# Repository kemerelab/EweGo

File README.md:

# EweGo

**Extensible Wearable for Egocentric and Group Observation**

EweGo is an open, animal-borne wearable that records the sensorium of each
animal in a group. It captures synchronized vision, audio, motion and RTK position, so we
can study collective behavior such as flocking, social learning and responses
to stress, with the aim of bringing it into neuroscience experiments. It was
built for sheep and is meant to be adapted to other species.

Each wearable is a Raspberry Pi CM4 on the **eweSAW** carrier board, with two
USB cameras, a u-blox ZED-X20P GNSS receiver, a BNO055 IMU, stereo
microphones and a battery fuel gauge. Every sample gets a precise timestamp.
It mounts on a collar or on a head halter.

| Folder | Contents |
|---|---|
| `Hardware/` | eweSAW carrier, camera hub and EweFeel IMU boards (KiCad), case designs ([details](Hardware/README.md)) |
| `Firmware/` | sensor loggers and test tools |
| `image/` | CI-built, ready-to-flash image ([details](image/README.md)) |

## Flashing a wearable

In Raspberry Pi Imager, open *Options → Content Repository* and enter
`https://github.com/kemerelab/EweGo/releases/latest/download/imager.json`.
Pick the EweGo image, set the hostname, user and Wi-Fi, and flash.

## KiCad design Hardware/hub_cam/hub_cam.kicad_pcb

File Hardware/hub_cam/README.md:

# hub_cam: USB hub carrier for two cameras plus the hub_imu module

**Status:** schematic and PCB layout done, DRC clean (0 errors, 0 unconnected). Not fabricated yet; see [NOTES.md](NOTES.md) for history and next steps.

## Board

- 31.66 x 16.65 mm, 1.0 mm thick, 2 layers, JLCPCB standard rules (0.2 mm track/space, 0.6/0.3 mm vias).
- All SMD parts are on the top, so JLCPCB assembles one side only.
- The hub_imu module stacks on the back on J1.
- Host end: USB-C receptacle J4, with its mouth at the board edge.
- Camera end: a 4.8 mm shelf in front of the two camera connectors.
- Thread holes: 6 non-plated, 1.4 mm. Four are on the camera shelf, for lashing the camera cables (strain relief). Two are at the USB end, one on each side of the connector. All are for sewing the board to the harness straps.
- Dimensions are drawn on the User.Drawings layer (`dimensions_stage5.png`).

## Parts

| Ref | Part | LCSC / JLCPCB # | Role |
|---|---|---|---|
| U1 | FE1.1S-BQFN24B (QFN-24, 4x4 mm) | C6776948 (extended) | USB 2.0 high-speed 4-port hub |
| Y1 | 12 MHz crystal, 3225 package | C9002 | Hub clock. The FE1.1S has internal load capacitors, so none are fitted. |
| R1 | 2.7k 1%, 0603 | C13167 | REXT bias resistor |
| R2, R3 | 10k, 0402 | C25744 | XRSTJ pull-up, DRV pull-down (normal hub mode, charging off) |
| R4, R5 | 5.1k, 0402 | C25905 | CC1/CC2 pull-downs. They identify the board as a USB device, so C-to-C cables supply VBUS. |
| C1, C2 | 10 uF 0603, 100 nF 0402 | C96446, C1525 | 5 V input to the hub |
| C3, C4 | 4.7 uF, 100 nF 0402 | C23733, C1525 | Output of the hub's internal 3.3 V regulator (VD33F) |
| C5 | 10 uF 0603 | C96446 | 5 V bulk capacitor at the camera connectors |
| U2, U3 | USBLC6-2SC6 (SOT-23-6) | C7519 (extended) | ESD protection at each camera connector. D-/D+ pass through pins 1-6 and 3-4. |
| J4 | USB-C receptacle, 16P, USB 2.0 (GCT USB4105 footprint) | C2765186 (extended) | Host connection. Shield to GND; SBU not connected. |
| J2, J3 | JST SH 4-pin, side entry (SM04B-SRSS-TB) | C160404 (extended) | Camera ports CAM1 / CAM2. Pinout: 1 VBUS, 2 D-, 3 D+, 4 GND |
| J1 | 1x4 2.54 mm pin header | hand-fitted | Stacking header for hub_imu. Same footprint and pin order as hub_imu's J1. |
| J5-J8 | Bare SMD pads on the back, 1.5 x 3 mm | - (copper only) | Backup host wiring if J4 is left off. Labelled on the silkscreen: 5V, D+, D-, GND. |

JLCPCB has no Basic-library USB-C or JST parts, so J2-J4 are Extended parts (an extended-part fee each).

### Camera cables (JST SH, crimped)

| Item | LCSC # | Note |
|---|---|---|
| Housing SHR-04V-S | C385125 | Not the NSHR variant |
| Contact SSH-003T-P0.2-H | C263995 | 28-32 AWG, insulation up to 0.8 mm OD |
| Crimper | - | For example Engineer PA-09 (1.0 mm die) |

## Port map

| Hub port | Connected to |
|---|---|
| 1 | CAM1 (J2) |
| 2 | IMU (J1) — middle pins, so its pair can drop to the top layer between the camera pairs |
| 3 | CAM2 (J3) |
| 4 | Unused |

## Hub configuration

- **Self-powered (BUSJ tied high).** The host then doesn't limit the cameras to 100 mA each. Nothing on the board limits or switches the camera power.
- **VBUSM and OVCJ tied to 3.3 V.** There is no over-current sensing.
- **ESD protection on the camera ports only.** The host USB-C port has none. That decision dates from the earlier design, when the host cable was soldered on permanently.

## Silkscreen

- Reference designators are hidden on the silkscreen because the board is too dense for them. They remain on the Fab layers.
- The top is labelled CAM1 / CAM2.
- The back is labelled with the wire-pad names and "hub_cam rev A 2026-10".

## License

The hardware design is licensed under the [CERN Open Hardware Licence v2, Permissive](LICENSE) (CERN-OHL-P-2.0).

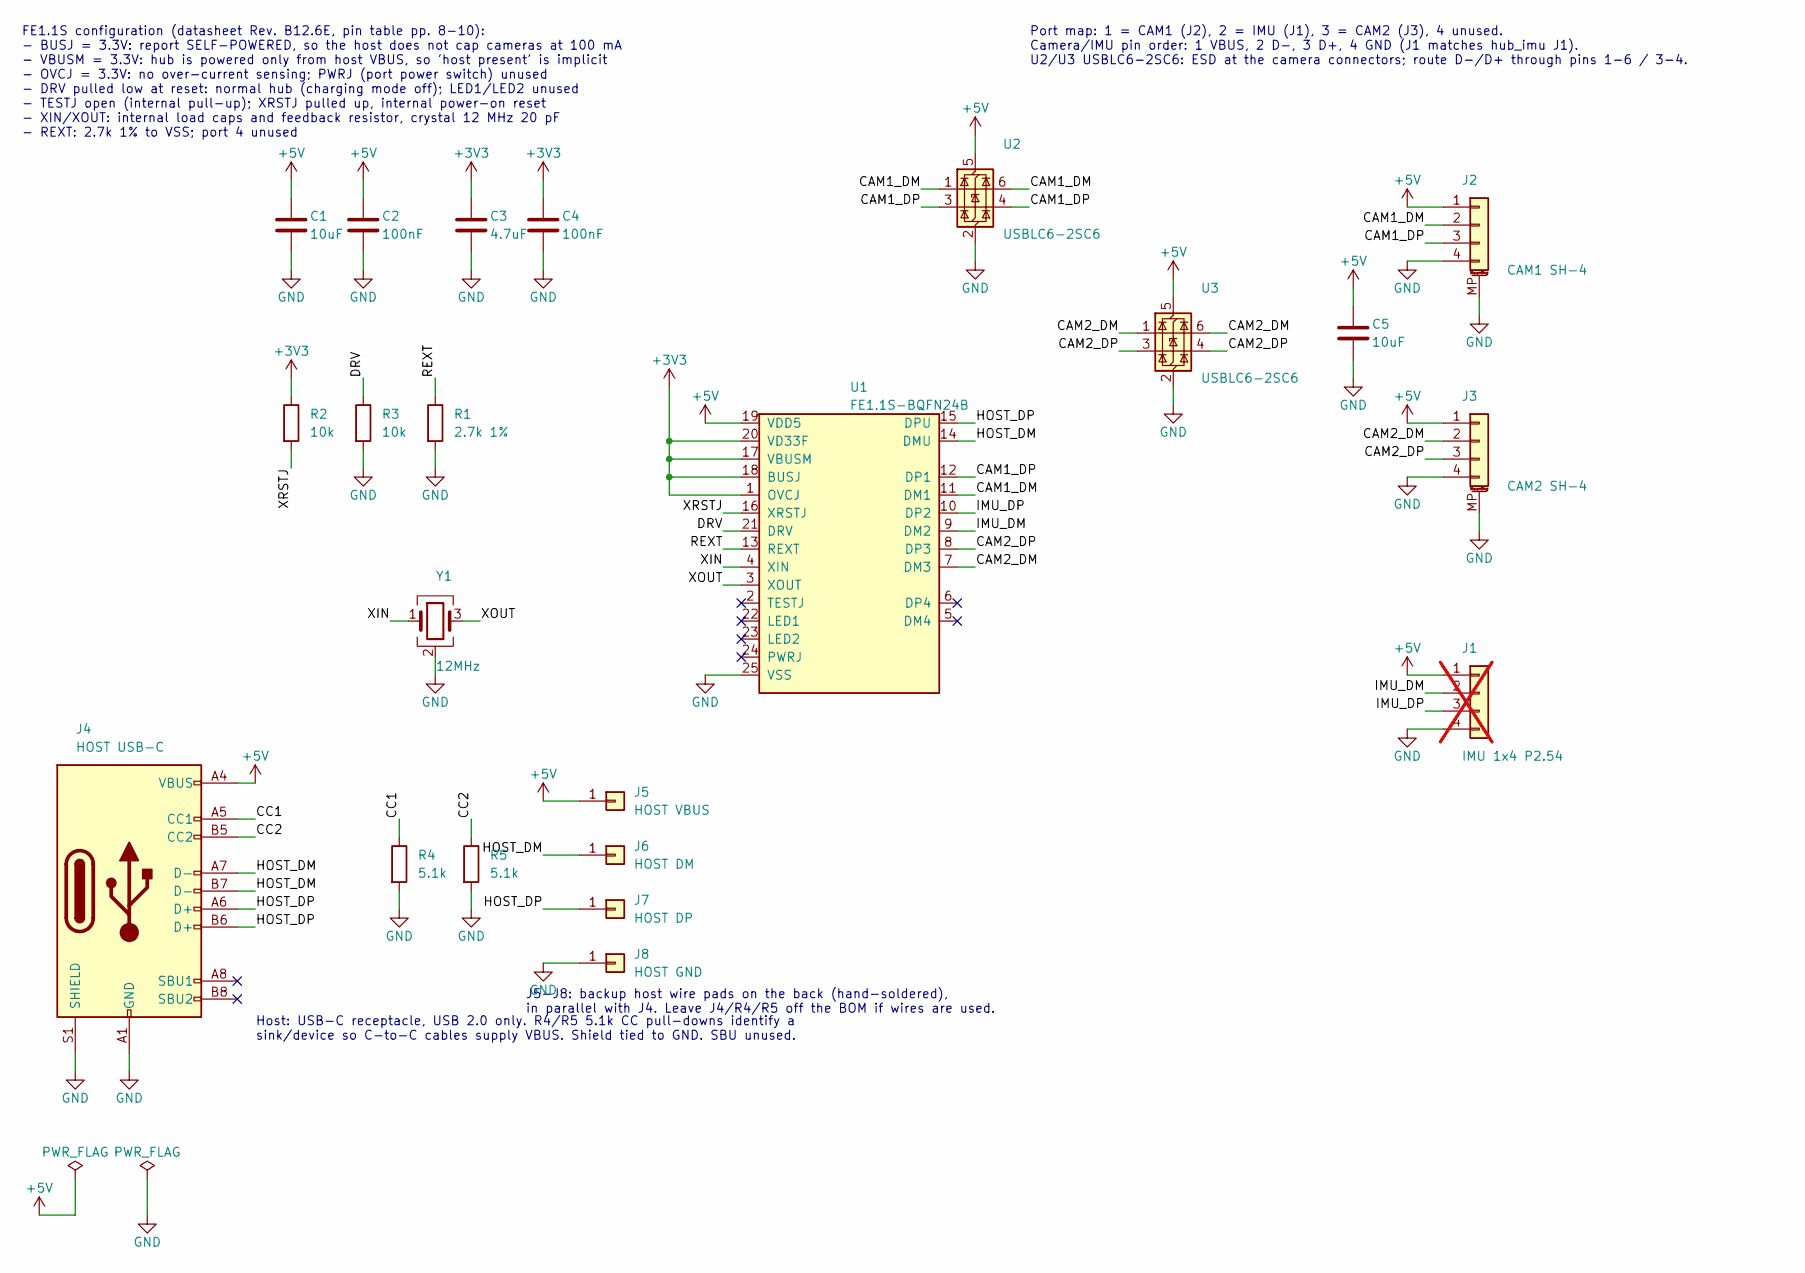
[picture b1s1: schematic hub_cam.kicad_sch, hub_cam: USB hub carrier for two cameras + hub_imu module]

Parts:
C1, C5: 10uF; C_0603_1608Metric; JLCPCB Part # C96446
C2, C4: 100nF; C_0402_1005Metric; JLCPCB Part # C1525
C3: 4.7uF; C_0402_1005Metric; JLCPCB Part # C23733
J1: IMU 1x4 P2.54; PinHeader_1x04_P2.54mm_Vertical; not fitted
J2: CAM1 SH-4; JST_SH_SM04B-SRSS-TB_1x04-1MP_P1.00mm_Horizontal; JLCPCB Part # C160404
J3: CAM2 SH-4; JST_SH_SM04B-SRSS-TB_1x04-1MP_P1.00mm_Horizontal; JLCPCB Part # C160404
J4: HOST USB-C; USB_C_Receptacle_GCT_USB4105-xx-A_16P_TopMnt_Horizontal; JLCPCB Part # C2765186
J5: HOST VBUS; SolderWirePad_1x01_SMD_1.5x3mm
J6: HOST DM; SolderWirePad_1x01_SMD_1.5x3mm
J7: HOST DP; SolderWirePad_1x01_SMD_1.5x3mm
J8: HOST GND; SolderWirePad_1x01_SMD_1.5x3mm
R1: 2.7k 1%; R_0603_1608Metric; JLCPCB Part # C13167
R2, R3: 10k; R_0402_1005Metric; JLCPCB Part # C25744
R4, R5: 5.1k; R_0402_1005Metric; JLCPCB Part # C25905
U1: FE1.1S-BQFN24B; QFN-24-1EP_4x4mm_P0.5mm_EP2.6x2.6mm; JLCPCB Part # C6776948
U2, U3: USBLC6-2SC6; SOT-23-6; JLCPCB Part # C7519
Y1: 12MHz; Crystal_SMD_3225-4Pin_3.2x2.5mm; JLCPCB Part # C9002

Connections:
+3V3: C3.1, C4.1, R2.1, U1.1 (OVCJ), U1.17 (VBUSM), U1.18 (BUSJ), U1.20 (VD33F)
+5V: C1.1, C2.1, C5.1, J1.1, J2.1, J3.1, J4.A4 (VBUS), J4.A9 (VBUS), J4.B4 (VBUS), J4.B9 (VBUS), J5.1, U1.19 (VDD5), U2.5 (VBUS), U3.5 (VBUS)
/CAM1_DM: J2.2, U1.11 (DM1), U2.1 (I/O1), U2.6 (I/O1)
/CAM1_DP: J2.3, U1.12 (DP1), U2.3 (I/O2), U2.4 (I/O2)
/CAM2_DM: J3.2, U1.7 (DM3), U3.1 (I/O1), U3.6 (I/O1)
/CAM2_DP: J3.3, U1.8 (DP3), U3.3 (I/O2), U3.4 (I/O2)
/CC1: J4.A5 (CC1), R4.1
/CC2: J4.B5 (CC2), R5.1
/DRV: R3.1, U1.21 (DRV)
/HOST_DM: J4.A7 (D-), J4.B7 (D-), J6.1, U1.14 (DMU)
/HOST_DP: J4.A6 (D+), J4.B6 (D+), J7.1, U1.15 (DPU)
/IMU_DM: J1.2, U1.9 (DM2)
/IMU_DP: J1.3, U1.10 (DP2)
/REXT: R1.1, U1.13 (REXT)
/XIN: U1.4 (XIN), Y1.1
/XOUT: U1.3 (XOUT), Y1.3
/XRSTJ: R2.2, U1.16 (XRSTJ)
GND: C1.2, C2.2, C3.2, C4.2, C5.2, J1.4, J2.4, J2.MP (MountPin), J3.4, J3.MP (MountPin), J4.A1 (GND), J4.A12 (GND), J4.B1 (GND), J4.B12 (GND), J4.S1 (SHIELD), J8.1, R1.2, R3.2, R4.2, R5.2, U1.25 (VSS), U2.2 (GND), U3.2 (GND), Y1.2 (G), Y1.4 (G)

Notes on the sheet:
FE1.1S configuration (datasheet Rev. B12.6E, pin table pp. 8-10): - BUSJ = 3.3V: report SELF-POWERED, so the host does not cap cameras at 100 mA - VBUSM = 3.3V: hub is powered only from host VBUS, so 'host present' is implicit - OVCJ = 3.3V: no over-current sensing; PWRJ (port power switch) unused 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
Port map: 1 = CAM1 (J2), 2 = IMU (J1), 3 = CAM2 (J3), 4 unused. Camera/IMU pin order: 1 VBUS, 2 D-, 3 D+, 4 GND (J1 matches hub_imu J1). U2/U3 USBLC6-2SC6: ESD at the camera connectors; route D-/D+ through pins 1-6 / 3-4.
J5-J8: backup host wire pads on the back (hand-soldered), in parallel with J4. Leave J4/R4/R5 off the BOM if wires are used.
Host: USB-C receptacle, USB 2.0 only. R4/R5 5.1k CC pull-downs identify a sink/device so C-to-C cables supply VBUS. Shield tied to GND. SBU unused.

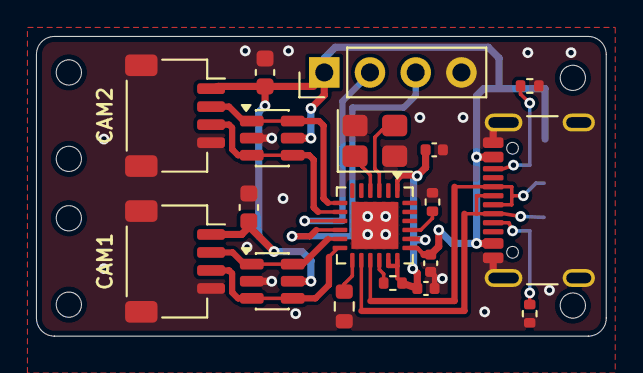
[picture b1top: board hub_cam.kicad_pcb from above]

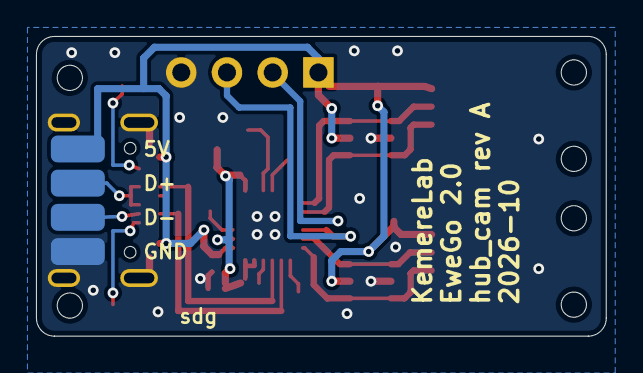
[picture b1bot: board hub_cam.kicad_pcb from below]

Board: 2 copper layers, 31.7 x 16.7 mm, 22 parts (4 on the bottom side), 18 nets.

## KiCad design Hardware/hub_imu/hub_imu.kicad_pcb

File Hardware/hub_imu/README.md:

# hub_imu: USB IMU module for FE1.1S USB 2.0 hubs

A small 2-layer module that stacks onto a USB 2.0 hub board built around the
Terminus **FE1.1S** hub IC, such as
[these hubs on Amazon](https://www.amazon.com/dp/B0GTVPVPV9). It plugs into one of the
hub's downstream ports through a 0.1" 1x4 header and appears on the host as a
USB device that bridges to a Bosch BNO055 9-axis IMU over I2C.

- **Board:** 21.0 x 14.4 mm, 2 layers, 1.6 mm FR4, 1 oz copper (JLCPCB standard rules)
- **Tools:** KiCad 9.0

| Top | Bottom |
|---|---|
|  |  |

The renders come from KiCad's 3D viewer. The J1 and J2 headers are marked do-not-populate (hand-soldered), so they don't appear.

### Photos

| Assembled module | Next to an FE1.1S hub | Stacked onto the hub |
|---|---|---|
|  |  |  |

## Contents

| File | What it is |
|---|---|
| `hub_imu.kicad_pro` / `.kicad_sch` / `.kicad_pcb` | KiCad project, schematic, layout |
| `hub_imu.kicad_dru` | Custom design rules (see below) |
| `stage1.svg` ... `stage5.svg` | Layout renders (F.Cu, B.Cu, F.SilkS, Edge.Cuts) after placement, power, USB, signals, pours |
| `drc_stage1.rpt` ... `drc_stage5.rpt` | DRC report after each stage (`drc_stage5.rpt` is the final one) |
| `production/hub_imu.zip` | Gerbers and drill files for JLCPCB (from the Fabrication Toolkit plugin) |
| `images/` | 3D renders and photos used in this README |
| `firmware/` | STM32F042 firmware, built by CI ([README](firmware/README.md)) |
| `NOTES.md` | history, status and gotchas for whoever picks this up next |

## Circuit

| Ref | Part | JLCPCB # (basic) | Role |
|---|---|---|---|
| U1 | STM32F042F6P6 (TSSOP-20) | - (not basic) | Crystal-less USB FS device, USB-to-I2C bridge |
| U2 | BNO055 (LGA-28) | - (not basic) | 9-axis IMU, I2C mode (PS0 = PS1 = GND), address 0x28 (COM3 = GND) |
| U3 | XC6206P332MR (SOT-23-3) | C5446 | 5 V to 3.3 V LDO, 200 mA (pins: 1 VSS, 2 VOUT, 3 VIN), the only heat source |
| J1 | 1x4 2.54 mm header | - (hand-solder) | Connection to the hub |
| J2 | 2x3 1.27 mm header | - (hand-solder) | SWD programming/debug |
| D1 | Red LED, 0603 (KT-0603R) | C2286 | Status LED on PA3 |
| R5 | 1k 0402 | C11702 | LED resistor (~1.3 mA) |
| R3, R4 | 4.7k 0402 | C25900 | I2C pull-ups |
| R1, R2 | 10k 0402 | C25744 | BOOT0 pull-down, BNO055 nRESET pull-up |
| C1 | 1 uF 0402, 25 V X5R | C52923 | LDO input (+5V) |
| C2 | 4.7 uF 0402, 10 V X5R | C23733 | LDO output (+3V3) |
| C3-C8 | 100 nF 0402, 16 V X7R | C1525 | NRST filter; decoupling (U1 VDD, U1 VDDA, U2 VDD, U2 VDDIO, U2 CAP) |

Every assembled part has a `JLCPCB Part #` field in the schematic and PCB, taken from
[JLCPCB's basic parts library](https://jlcpcb.com/parts/basic_parts). U1, U2, J1 and J2
have the field left blank: the ICs aren't basic parts, and the headers are fitted by hand.

### J1 - hub connector (0.1" pitch)

| Pin | Signal |
|---|---|
| 1 | +5V (VBUS) |
| 2 | USB D- |
| 3 | USB D+ |
| 4 | GND |

This pin order has been checked against the hub's downstream-port header.

### J2 - SWD (2x3, 1.27 mm)

| Pin | Signal | Pin | Signal |
|---|---|---|---|
| 1 | +3V3 | 2 | BOOT0 |
| 3 | SWDIO | 4 | SWCLK |
| 5 | NRST | 6 | GND |

This is a custom pinout, not a standard ARM SWD connector, so an adapter or cable is needed.

## Firmware notes (STM32F042F6P6)

| Function | Pin |
|---|---|
| USB D- / D+ | PA11 / PA12 on pins 17/18. **Set `SYSCFG_CFGR1.PA11_PA12_RMP`**, or USB will not enumerate (these pins default to PA9/PA10). |
| I2C1 SDA / SCL | PF0 / PF1 (AF1) |
| BNO055 INT | PA5 (pin 11), EXTI |
| BNO055 nRESET | PA6 (pin 12), drive low to reset (10k pull-up on board) |
| Status LED | PA3 (pin 9), active high, ~1.3 mA (red 0603 LED + 1k) |
| SWD | PA13 / PA14 |

Use the internal HSI48 clock with CRS synced to USB SOF. There is no crystal, and the BNO055's 32 kHz crystal pins are left open (internal clock).

## Layout notes

- All components are on the top side.
- The bottom layer is a GND plane that also carries +3V3 distribution. Signals are on top, apart from four short jumpers: SDA under SCL, and BOOT0 / SWDIO to J2's through-hole pins.
- The USB D+/D- pair is 0.25 mm wide with a 0.2 mm gap, has no vias, and is length-matched (0 mm skew). Solid ground runs underneath it (bottom-layer track/via keepout `USB_BCu_keepout`).
- There are no bottom-layer tracks or vias under the IMU (`U2_BCu_keepout`), and no top copper inside U2's pad ring (`U2_FCu_interior`).
- Every decoupling cap is within 2 mm of the pin it serves and has an adjacent GND via.

### Custom design rules (`hub_imu.kicad_dru`)

- 0.2 mm minimum track and clearance; vias 0.6 mm pad / 0.3 mm drill.
- +5V / +3V3 tracks are 0.4 mm, necking to 0.25 mm only inside U2's courtyard (its pads are 0.254 mm wide).
- USB tracks are exactly 0.25 mm.
- No bottom-layer tracks or vias intersecting U2's courtyard.
- R1 and U1 GND pads may have one thermal spoke; both also have a direct track to a GND via.

## Verification status

The final DRC (`drc_stage5.rpt`) shows **0 errors and 0 unconnected pads**. The remaining items are
`lib_footprint_mismatch` warnings on the 0402, SOT-23-3 and LGA footprints. They come from KiCad re-save
rounding on rotated footprints, not from real geometry changes.

ERC reports only `lib_symbol_issues`, because the `hubimu` symbols are embedded in the schematic
rather than installed as a library.

## BNO055 datasheet check

Checked against Bosch BST-BNO055-DS000-18 (rev 1.8, Oct 2021); page numbers are the datasheet's own:

- **Reserved pins:** Table 5-1 (p. 106) marks PIN1, 12, 13, 15, 16, 21-24 and BL_IND (10) as "Do not connect". All are unconnected here.
- **Protocol/address pins:** PS1, PS0, COM2 and COM3 are tied to GND for I2C at 0x28 (Tables 4-4/4-5, p. 99; PS pins must not float).
- **XIN32/XOUT32:** left open for the internal clock (sec. 5.5.2, p. 111; internal clock tolerance up to ±3%).
- **CAP (9):** Fig. 9 (p. 107) shows 120 nF. C8 is 100 nF because there is no 120 nF JLCPCB basic part, and the figure's values are "typical example" only (footnote 9, p. 110).
- **nBOOT_LOAD_PIN (4):** Fig. 9 shows an optional 10k pull-up. Here it is tied directly to +3V3, so the part always boots the application (sec. 3.10, p. 51). The BNO055's own firmware cannot be updated on this board.

## Design decisions

- MCU decoupling is 100 nF each on VDD and VDDA, plus 4.7 uF at the LDO output on the same short +3V3 net. ST's usual guidance also suggests 1 uF + 10 nF on VDDA. This was judged unnecessary here: the supply traces are short, and the ADC is not used for anything precision-critical.

There are no open items.

## License

The hardware design is licensed under the [CERN Open Hardware Licence v2, Permissive](LICENSE) (CERN-OHL-P-2.0).

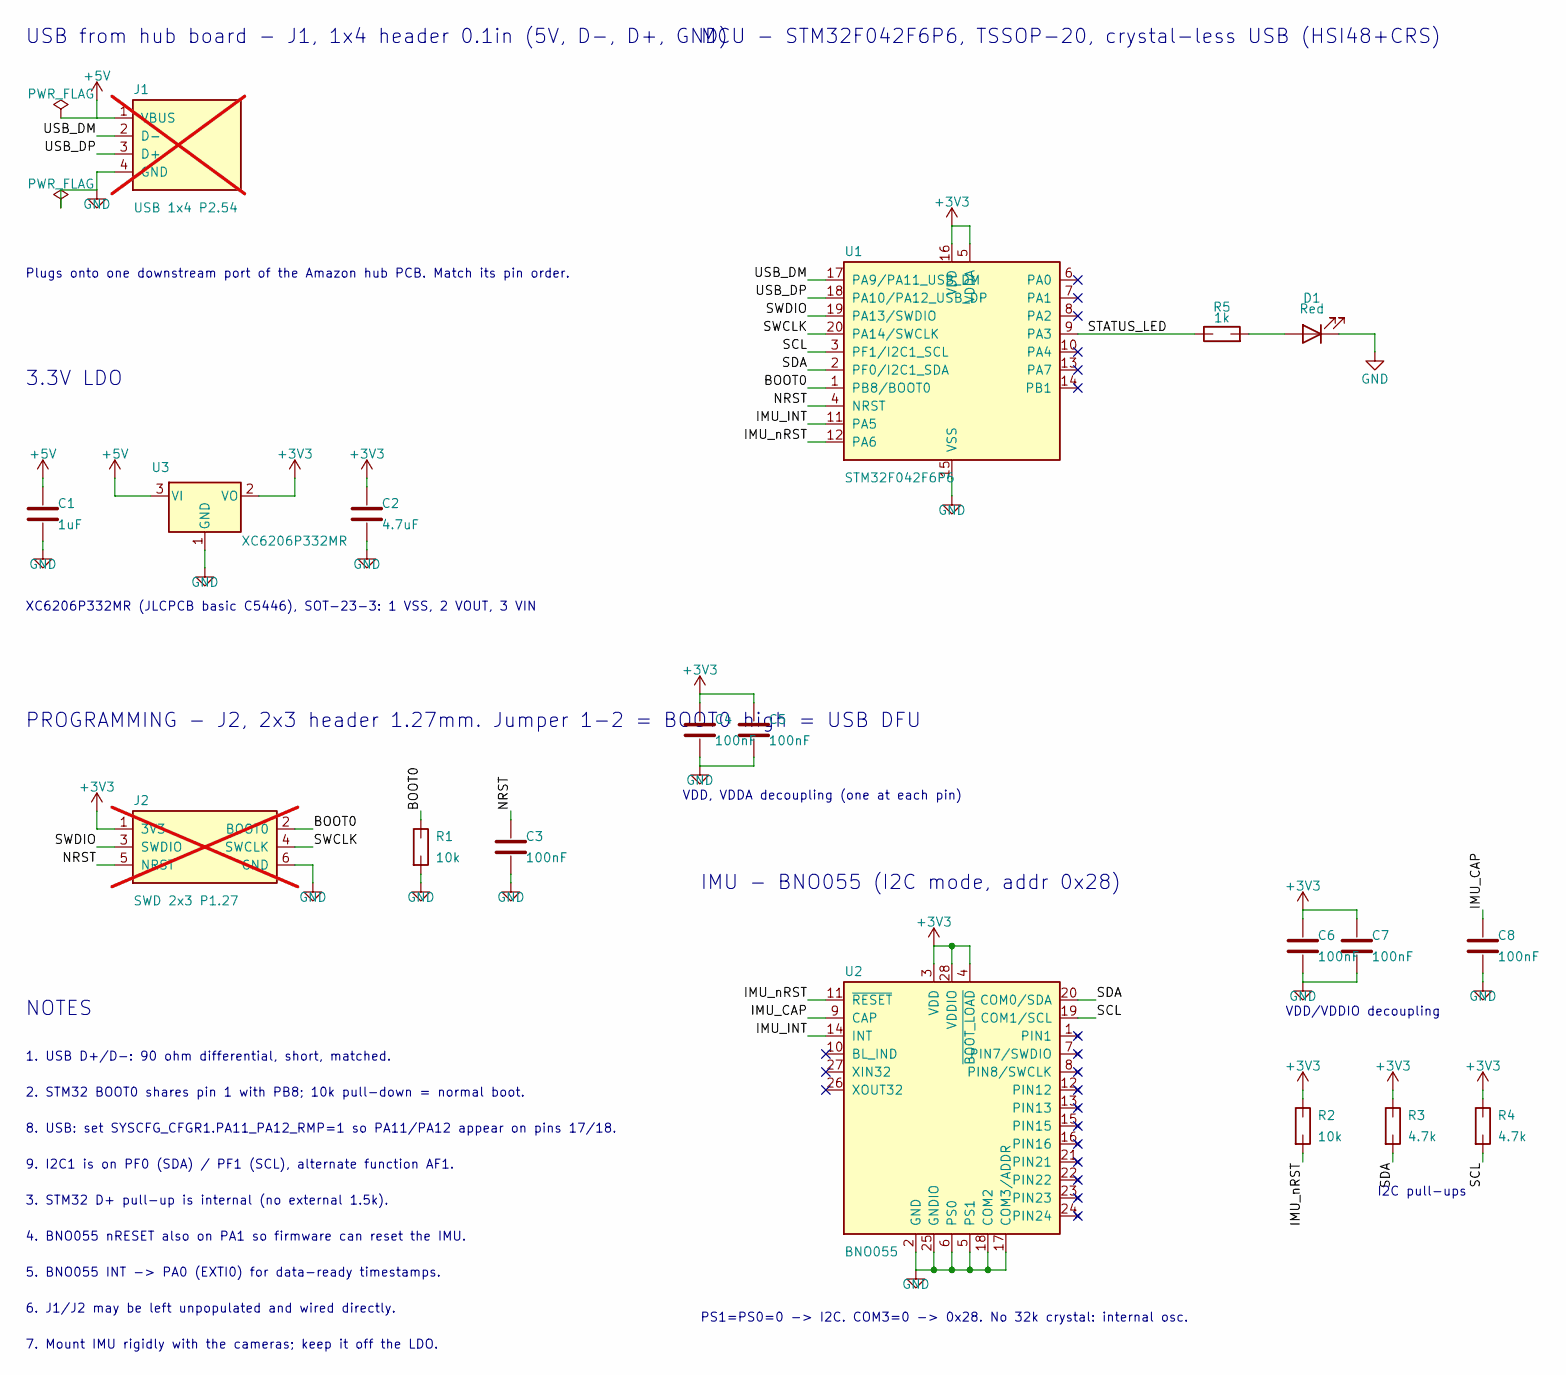
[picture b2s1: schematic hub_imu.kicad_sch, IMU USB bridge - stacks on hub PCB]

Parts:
C1: 1uF; C_0402_1005Metric; JLCPCB Part # C52923
C2: 4.7uF; C_0402_1005Metric; JLCPCB Part # C23733
C3, C4, C5, C6, C7, C8: 100nF; C_0402_1005Metric; JLCPCB Part # C1525
D1: Red; LED_0603_1608Metric; JLCPCB Part # C2286
J1: USB 1x4 P2.54; PinHeader_1x04_P2.54mm_Vertical; not fitted
J2: SWD 2x3 P1.27; PinHeader_2x03_P1.27mm_Vertical; not fitted
R1, R2: 10k; R_0402_1005Metric; JLCPCB Part # C25744
R3, R4: 4.7k; R_0402_1005Metric; JLCPCB Part # C25900
R5: 1k; R_0402_1005Metric; JLCPCB Part # C11702
U1: STM32F042F6P6; TSSOP-20_4.4x6.5mm_P0.65mm
U2: BNO055; LGA-28_5.2x3.8mm_P0.5mm
U3: XC6206P332MR; SOT-23-3; JLCPCB Part # C5446

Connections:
+3V3: C2.1, C4.1, C5.1, C6.1, C7.1, J2.1 (3V3), R2.1, R3.1, R4.1, U1.5 (VDDA), U1.16 (VDD), U2.3 (VDD), U2.4 (~BOOT_LOAD), U2.28 (VDDIO), U3.2 (VO)
+5V: C1.1, J1.1 (VBUS), U3.3 (VI)
/BOOT0: J2.2 (BOOT0), R1.1, U1.1 (PB8/BOOT0)
/IMU_CAP: C8.1, U2.9 (CAP)
/IMU_INT: U1.11 (PA5), U2.14 (INT)
/IMU_nRST: R2.2, U1.12 (PA6), U2.11 (~RESET)
/NRST: C3.1, J2.5 (NRST), U1.4 (NRST)
/SCL: R4.2, U1.3 (PF1/I2C1_SCL), U2.19 (COM1/SCL)
/SDA: R3.2, U1.2 (PF0/I2C1_SDA), U2.20 (COM0/SDA)
/STATUS_LED: R5.1, U1.9 (PA3)
/SWCLK: J2.4 (SWCLK), U1.20 (PA14/SWCLK)
/SWDIO: J2.3 (SWDIO), U1.19 (PA13/SWDIO)
/USB_DM: J1.2 (D-), U1.17 (PA9/PA11_USB_DM)
/USB_DP: J1.3 (D+), U1.18 (PA10/PA12_USB_DP)
GND: C1.2, C2.2, C3.2, C4.2, C5.2, C6.2, C7.2, C8.2, D1.1 (K), J1.4 (GND), J2.6 (GND), R1.2, U1.15 (VSS), U2.2 (GND), U2.5 (PS1), U2.6 (PS0), U2.17 (COM3/ADDR), U2.18 (COM2), U2.25 (GNDIO), U3.1 (GND)
unnamed: D1.2 (A), R5.2

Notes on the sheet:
3. STM32 D+ pull-up is internal (no external 1.5k).
Plugs onto one downstream port of the Amazon hub PCB. Match its pin order.
IMU - BNO055 (I2C mode, addr 0x28)
8. USB: set SYSCFG_CFGR1.PA11_PA12_RMP=1 so PA11/PA12 appear on pins 17/18.
PROGRAMMING - J2, 2x3 header 1.27mm. Jumper 1-2 = BOOT0 high = USB DFU
7. Mount IMU rigidly with the cameras; keep it off the LDO.
9. I2C1 is on PF0 (SDA) / PF1 (SCL), alternate function AF1.
I2C pull-ups
USB from hub board - J1, 1x4 header 0.1in (5V, D-, D+, GND)
VDD, VDDA decoupling (one at each pin)
PS1=PS0=0 -> I2C. COM3=0 -> 0x28. No 32k crystal: internal osc.
5. BNO055 INT -> PA0 (EXTI0) for data-ready timestamps.
1. USB D+/D-: 90 ohm differential, short, matched.
6. J1/J2 may be left unpopulated and wired directly.
NOTES
VDD/VDDIO decoupling
MCU - STM32F042F6P6, TSSOP-20, crystal-less USB (HSI48+CRS)
3.3V LDO
XC6206P332MR (JLCPCB basic C5446), SOT-23-3: 1 VSS, 2 VOUT, 3 VIN
4. BNO055 nRESET also on PA1 so firmware can reset the IMU.
2. STM32 BOOT0 shares pin 1 with PB8; 10k pull-down = normal boot.

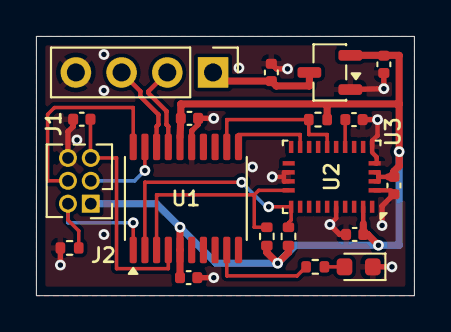
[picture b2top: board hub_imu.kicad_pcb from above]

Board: 2 copper layers, 21.0 x 14.4 mm, 19 parts (0 on the bottom side), 16 nets.

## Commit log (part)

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2026-01-03 Updated dual camera script with excess removed
